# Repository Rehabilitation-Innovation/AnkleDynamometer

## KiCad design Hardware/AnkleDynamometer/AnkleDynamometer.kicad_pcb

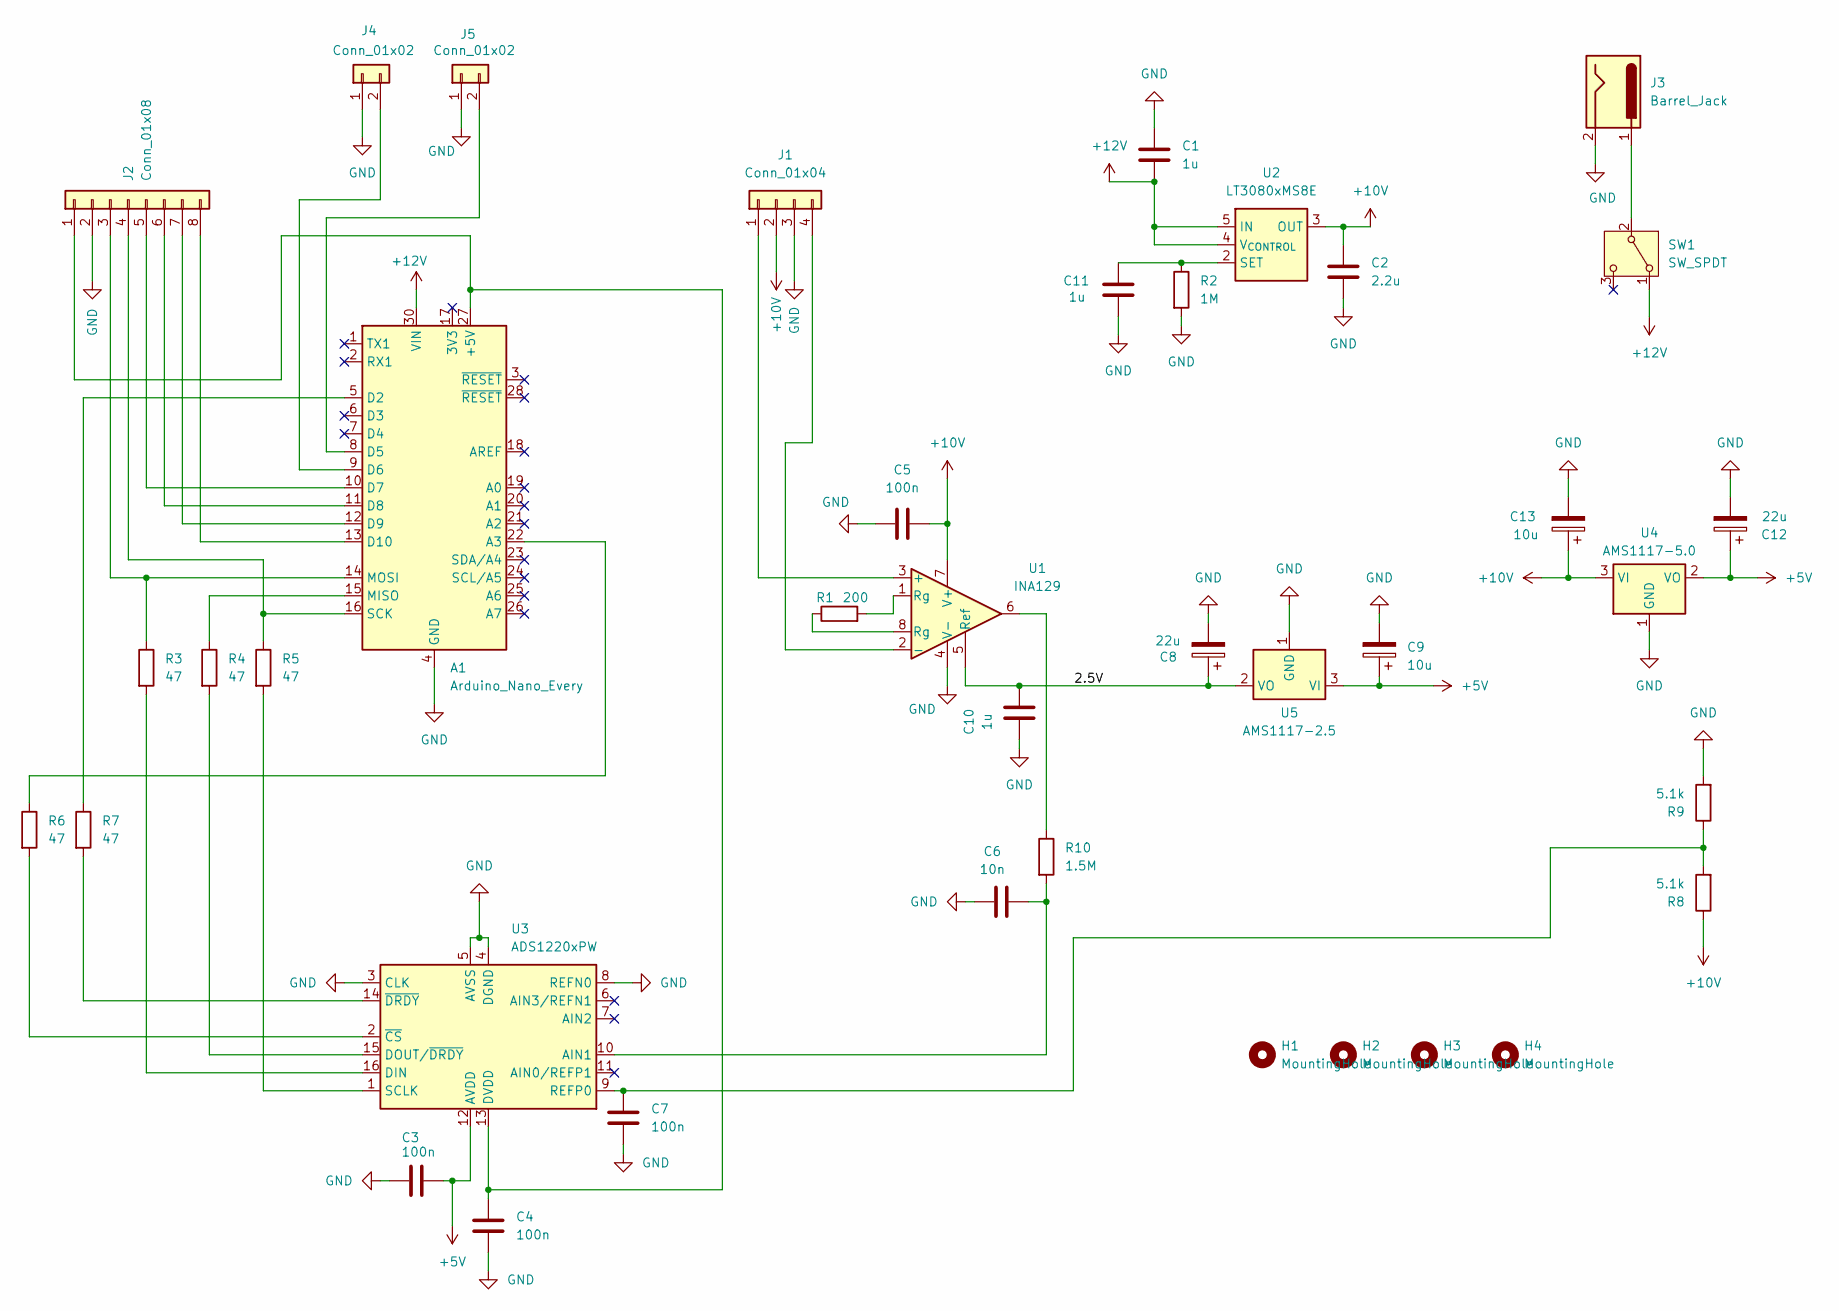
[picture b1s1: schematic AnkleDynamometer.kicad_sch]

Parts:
A1: Arduino_Nano_Every; Arduino_Nano
C1, C10, C11: 1u; C_0805_2012Metric; LCSC C28323
C2: 2.2u; C_1206_3216Metric; LCSC C50254
C3, C4, C5, C7: 100n; C_0603_1608Metric; LCSC C14663
C6: 10n; C_0603_1608Metric; LCSC C85973
C8, C12: 22u; CP_EIA-3216-18_Kemet-A; LCSC C11366
C9, C13: 10u; CP_EIA-3216-18_Kemet-A; LCSC C7171
H1, H2, H3, H4: MountingHole; MountingHole_2.2mm_M2_Pad_Via
J1: Conn_01x04; JST_EH_B4B-EH-A_1x04_P2.50mm_Vertical
J2: Conn_01x08; JST_EH_B8B-EH-A_1x08_P2.50mm_Vertical
J3: Barrel_Jack; BarrelJack_Horizontal
J4, J5: Conn_01x02; JST_EH_B2B-EH-A_1x02_P2.50mm_Vertical
R1: 200; R_0603_1608Metric_Pad0.98x0.95mm_HandSolder; LCSC C8218
R2: 1M; R_0603_1608Metric_Pad0.98x0.95mm_HandSolder; LCSC C22935
R3, R4, R5, R6, R7: 47; R_0603_1608Metric_Pad0.98x0.95mm_HandSolder; LCSC C23182
R8, R9: 5.1k; R_0603_1608Metric_Pad0.98x0.95mm_HandSolder; LCSC C23186
R10: 1.5M; R_0603_1608Metric_Pad0.98x0.95mm_HandSolder; LCSC C137773
SW1: SW_SPDT; SW_SLW-121586-5A-D
U1: INA129; DIP-8_W7.62mm
U2: LT3080xMS8E; TO-263-5_TabPin3; LCSC C580029
U3: ADS1220xPW; TSSOP-16_4.4x5mm_P0.65mm; LCSC C48263
U4: AMS1117-5.0; SOT-223-3_TabPin2; LCSC C6187
U5: AMS1117-2.5; SOT-223-3_TabPin2; LCSC C12087

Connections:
+5V: C3.1, C9.1, C12.1, U3.12 (AVDD), U4.2 (VO), U5.3 (VI)
+10V: C2.1, C5.2, C13.1, J1.2, R8.1, U1.7 (V+), U2.3 (OUT), U4.3 (VI)
+12V: A1.30 (VIN), C1.2, SW1.1 (A), U2.4 (V_{CONTROL}), U2.5 (IN)
/2.5V: C8.1, C10.2, U1.5 (Ref), U5.2 (VO)
GND: A1.4 (GND), A1.29 (GND), C1.1, C2.2, C3.2, C4.1, C5.1, C6.1, C7.1, C8.2, C9.2, C10.1, C11.2, C12.2, C13.2, J1.3, J2.2, J3.2, J4.1, J5.1, R2.2, R9.2, U1.4 (V-), U3.3 (CLK), U3.4 (DGND), U3.5 (AVSS), U3.8 (REFN0), U4.1 (GND), U5.1 (GND)
unnamed: A1.27 (+5V), C4.2, J2.1, U3.13 (DVDD)
unnamed: A1.22 (A3), R6.1
unnamed: A1.5 (D2), R7.1
unnamed: A1.8 (D5), J5.2
unnamed: A1.9 (D6), J4.2
unnamed: A1.10 (D7), J2.5
unnamed: A1.11 (D8), J2.6
unnamed: A1.12 (D9), J2.7
unnamed: A1.13 (D10), J2.8
unnamed: A1.15 (MISO), R4.1
unnamed: A1.14 (MOSI), J2.3, R3.1
unnamed: A1.16 (SCK), J2.4, R5.1
unnamed: J1.1, U1.3 (+)
unnamed: J1.4, U1.2 (-)
unnamed: R1.1, U1.8 (Rg)
unnamed: R1.2, U1.1 (Rg)
unnamed: R10.1, U1.6
unnamed: J3.1, SW1.2 (B)
unnamed: C11.1, R2.1, U2.2 (SET)
unnamed: C6.2, R10.2, U3.10 (AIN1)
unnamed: R3.2, U3.16 (DIN)
unnamed: R4.2, U3.15 (DOUT/~DRDY)
unnamed: C7.2, R8.2, R9.1, U3.9 (REFP0)
unnamed: R5.2, U3.1 (SCLK)
unnamed: R6.2, U3.2 (~CS)
unnamed: R7.2, U3.14 (~DRDY)

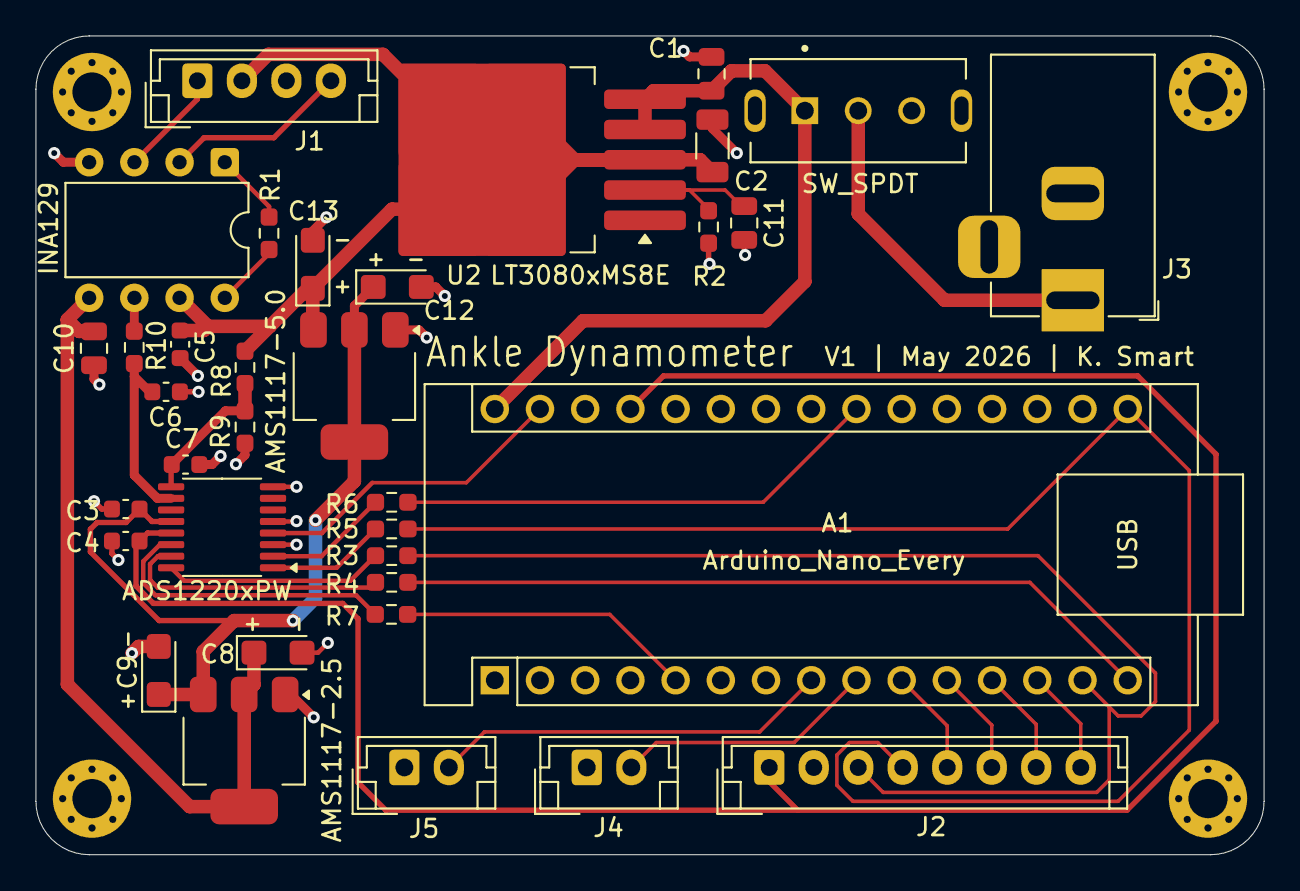
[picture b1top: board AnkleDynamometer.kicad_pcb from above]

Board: 2 copper layers, 69.0 x 46.0 mm, 39 parts (0 on the bottom side), 31 nets.

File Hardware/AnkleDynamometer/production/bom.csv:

Designator,Footprint,Quantity,Value,LCSC Part #
A1,Arduino_Nano,1,Arduino_Nano_Every,
"C1, C10, C11",0805,3,1u,C28323
C2,1206,1,2.2u, C50254
"C3, C4, C5, C7",0603,4,100n,C14663
C6,0603,1,10n,C85973
C8,CP_EIA-3216-18_Kemet-A,1,22u,C11366
C9,CP_EIA-3216-18_Kemet-A,1,10u, C7171
J1,JST_EH_B4B-EH-A_1x04_P2.50mm_Vertical,1,Conn_01x04,
J2,JST_EH_B8B-EH-A_1x08_P2.50mm_Vertical,1,Conn_01x08,
J3,BarrelJack_Horizontal,1,Barrel_Jack,
"J4, J5",JST_EH_B2B-EH-A_1x02_P2.50mm_Vertical,2,Conn_01x02,
R1,0603,1,200,C8218
R10,0603,1,1.5M,C137773
R2,0603,1,1M,C22935
"R3, R4, R5, R6, R7",0603,5,47,C23182
"R8, R9",0603,2,5.1k,C23186
SW1,SW_SLW-121586-5A-D,1,SW_SPDT,
U1,DIP-8_W7.62mm,1,INA129,
U2,TO-263-5_TabPin3,1,LT3080xMS8E,C580029
U3,TSSOP-16_4.4x5mm_P0.65mm,1,ADS1220xPW,C48263
U5,SOT-223-3_TabPin2,1,AMS1117-2.5,C12087

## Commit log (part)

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2026-01-30 I2C and filtering
2026-01-30 Create AnkleDynamometerCode.ino
    Operates readings, LCD screen, and reset/zero
2026-04-20 Reorganizing
    Reorganizing files
2026-04-20 Noise testing
    Uploading noise testing files
2026-04-22 LCD
    Added the LCD display code included with the display (https://www.waveshare.com/wiki/2inch_LCD_Module?amazon#Arduino_Software_Description) to the setup to test printing out values. Updating the scree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
2026-04-22 PCB
    Created and edited kiCAD project for hardware design
2026-04-23 LCD
    Added the LCD screen to the setup alongside the load cell system using the Adafruit ST7789 and Adafruit GFX libraries.
2026-04-23 PCB Schematic
    Put together the KiCAD schematic
2026-04-27 PCB
    Updating schematic
2026-05-04 PCB layout
2026-05-04 Removing unused files
2026-05-07 PCB layout 2
2026-06-29 Firmware updates
    - include zero and max reset buttons
    - calculating torque and rounding to the appropriate resolution
    - Updating display visuals
2026-06-29 PCB Noise Measurements
    Measuring and calculating the noise-free resolution with the PCB
2026-06-29 Load cell validation
    Calibrating load cell and checking repeatability and drift
